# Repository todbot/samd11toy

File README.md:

# samd11toy
playing with SAMD11

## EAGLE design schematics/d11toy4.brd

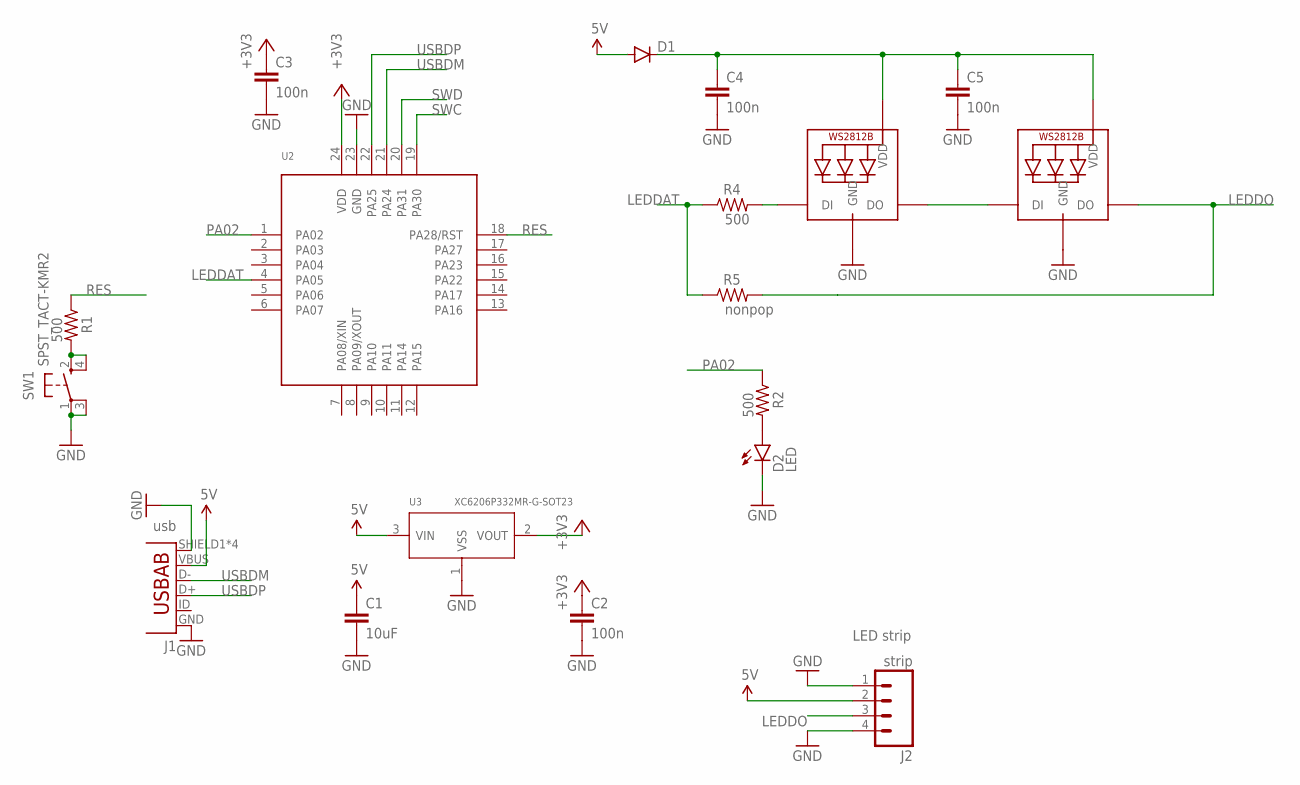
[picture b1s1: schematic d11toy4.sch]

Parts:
C1: 10uF; 0603-CAP
C2, C3, C4, C5: 100n; 0603-CAP
D1: DIODESOD523; SOD523
D2: LED; LED-0603
J1: usb; USB-AB-MICRO-SMD
J2: strip; 1X04_NO_SILK_ALL_ROUND
LED1, LED2: WS2812B5050; WS2812B
R1, R2, R4: 500; 0603-RES
R5: nonpop; 0603-RES
SW1: SPST_TACT-KMR2; KMR2
U2: SAMD11D14AM; QFN24
U3: XC6206P332MR-G-SOT23; SOT-23

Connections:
5V: C1.1, D1.A, J1.VBUS, J2.2, U3.3 (VIN)
+3V3: C2.1, C3.1, U2.24 (VDD), U3.2 (VOUT)
GND: C1.2, C2.2, C3.2, C4.2, C5.2, D2.C, J1.GND, J1.SHIELD1 (SHIELD), J1.SHIELD2 (SHIELD), J1.SHIELD3 (SHIELD), J1.SHIELD4 (SHIELD), J2.1, J2.4, LED1.3-GND (GND), LED2.3-GND (GND), SW1.1, SW1.3 (P1), U2.23 (GND), U3.1 (VSS)
LEDDAT: R4.1, R5.1, U2.4 (PA05)
LEDDO: J2.3, LED2.2-DOUT (DO), R5.2
unnamed: D2.A, R2.2
unnamed: R1.2, SW1.2 (S), SW1.4 (S1)
unnamed: LED1.2-DOUT (DO), LED2.4-DIN (DI)
unnamed: C4.1, C5.1, D1.C, LED1.1-VDD (VDD), LED2.1-VDD (VDD)
unnamed: LED1.4-DIN (DI), R4.2
PA02: R2.1, U2.1 (PA02)
RES: R1.1, U2.18 (PA28/RST)
SWC: U2.19 (PA30)
SWD: U2.20 (PA31)
USBDM: J1.D-, U2.21 (PA24)
USBDP: J1.D+, U2.22 (PA25)

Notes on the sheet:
LED strip

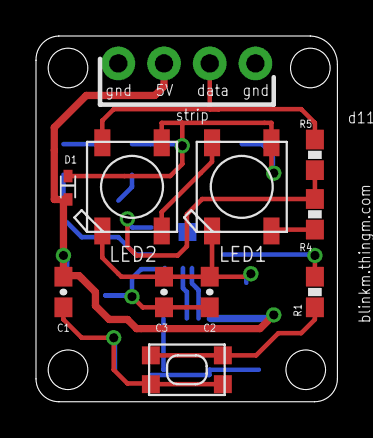
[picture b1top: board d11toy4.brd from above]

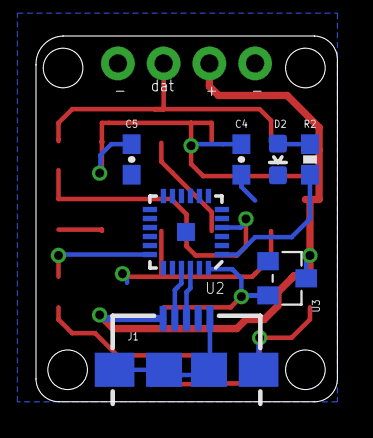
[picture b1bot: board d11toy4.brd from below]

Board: 2 copper layers, 16.7 x 20.3 mm, 18 parts (7 on the bottom side), 14 nets.

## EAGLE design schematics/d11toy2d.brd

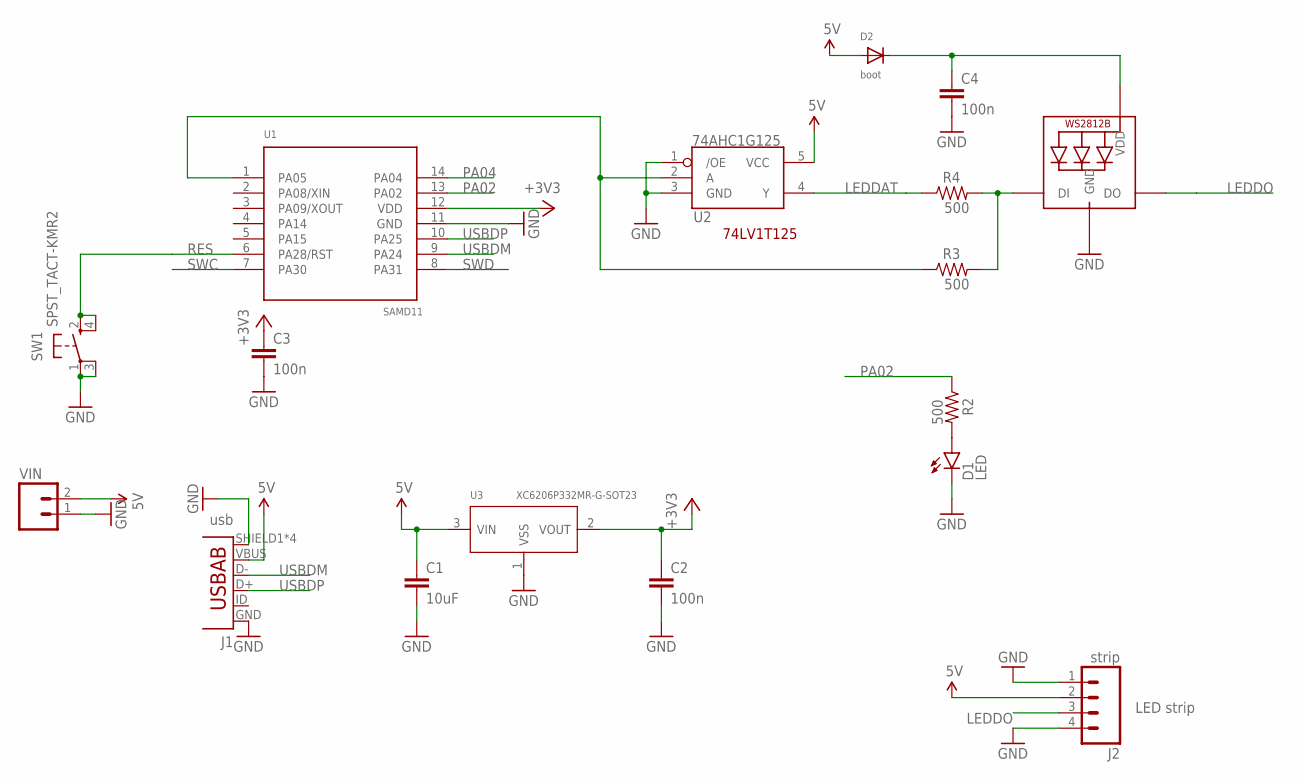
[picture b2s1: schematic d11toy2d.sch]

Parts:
C1: 10uF; 0603-CAP
C2, C3, C4: 100n; 0603-CAP
D1: LED; LED-0603
D2: boot; SOD-523
J1: usb; USB-AB-MICRO-SMD
J2: strip; 1X04_NO_SILK_ALL_ROUND
LED1: WS2812B5050; WS2812B
R2, R3, R4: 500; 0603-RES
SW1: SPST_TACT-KMR2; KMR2
U1: SAMD11; SO14
U2: 74AHC1G125; SOT23-5
U3: XC6206P332MR-G-SOT23; SOT-23
VIN: M02PTH; 1X02

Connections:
5V: C1.1, D2.A, J1.VBUS, J2.2, U2.5 (VCC), U3.3 (VIN), VIN.2
+3V3: C2.1, C3.1, U1.12 (VDD), U3.2 (VOUT)
GND: C1.2, C2.2, C3.2, C4.2, D1.C, J1.GND, J1.SHIELD1 (SHIELD), J1.SHIELD2 (SHIELD), J1.SHIELD3 (SHIELD), J1.SHIELD4 (SHIELD), J2.1, J2.4, LED1.3-GND (GND), SW1.1, SW1.3 (P1), U1.11 (GND), U2.1 (/OE), U2.3 (GND), U3.1 (VSS), VIN.1
LEDDAT: R4.1, U2.4 (Y)
LEDDAT3V3: R3.1, U1.1 (PA05), U2.2 (A)
LEDDO: J2.3, LED1.2-DOUT (DO)
unnamed: D1.A, R2.2
unnamed: C4.1, D2.K (C), LED1.1-VDD (VDD)
unnamed: LED1.4-DIN (DI), R3.2, R4.2
PA02: R2.1, U1.13 (PA02)
PA04: U1.14 (PA04)
RES: SW1.2 (S), SW1.4 (S1), U1.6 (PA28/RST)
SWC: U1.7 (PA30)
SWD: U1.8 (PA31)
USBDM: J1.D-, U1.9 (PA24)
USBDP: J1.D+, U1.10 (PA25)

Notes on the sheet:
LED strip
74LV1T125

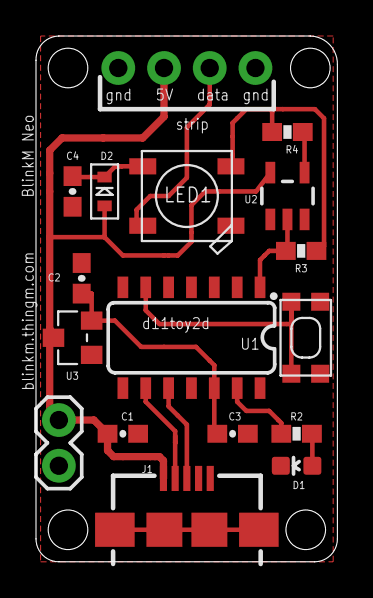
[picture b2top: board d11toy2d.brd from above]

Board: 2 copper layers, 16.7 x 29.2 mm, 17 parts (0 on the bottom side), 13 nets.

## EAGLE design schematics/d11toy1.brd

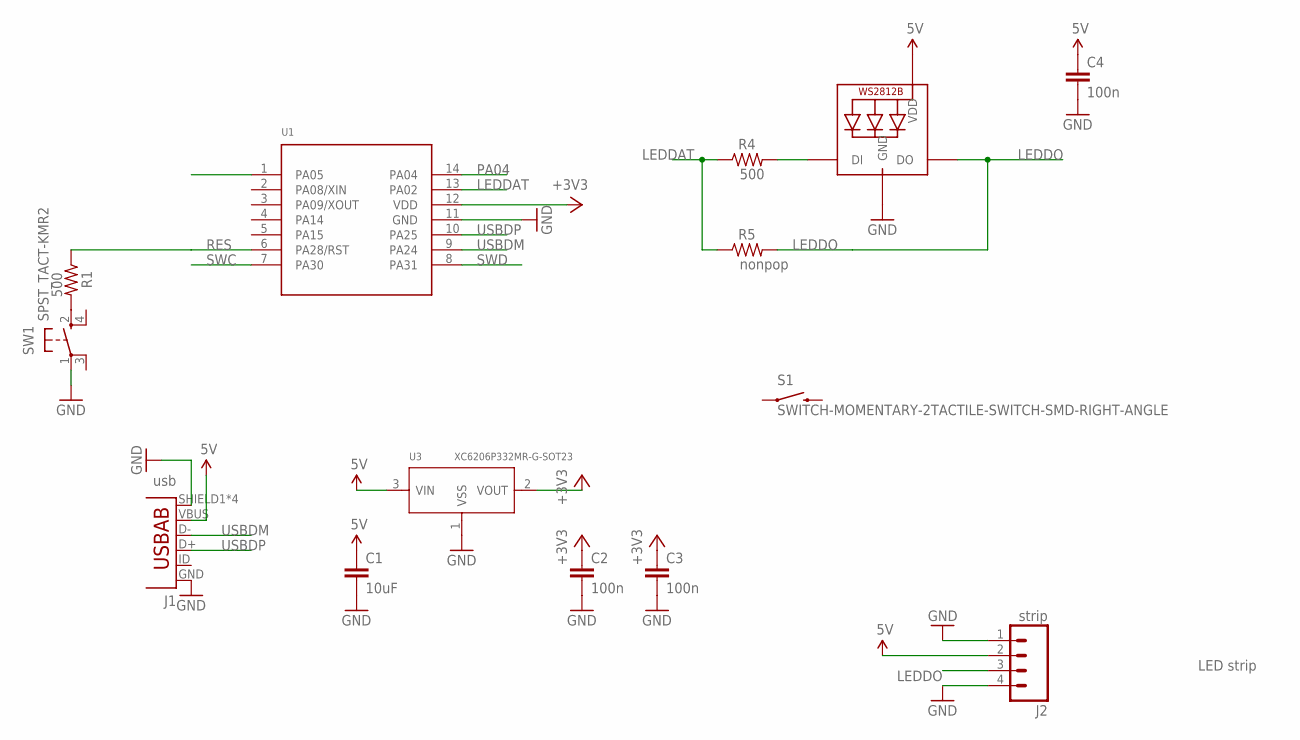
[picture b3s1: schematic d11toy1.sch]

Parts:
C1: 10uF; 0603-CAP
C2, C3, C4: 100n; 0603-CAP
J1: usb; USB-AB-MICRO-SMD
J2: strip; 1X04_NO_SILK_ALL_ROUND
LED1: WS2812B3535; LED3535
R1, R4: 500; 0603-RES
R5: nonpop; 0603-RES
S1: SWITCH-MOMENTARY-2TACTILE-SWITCH-SMD-RIGHT-ANGLE; TACTILE_SWITCH-SMD-RIGHT-ANGLE
SW1: SPST_TACT-KMR2; KMR2
U1: SAMD11C14; SO14
U3: XC6206P332MR-G-SOT23; SOT-23

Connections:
5V: C1.1, C4.1, J1.VBUS, J2.2, LED1.2 (VDD), U3.3 (VIN)
+3V3: C2.1, C3.1, U1.12 (VDD), U3.2 (VOUT)
GND: C1.2, C2.2, C3.2, C4.2, J1.GND, J1.SHIELD1 (SHIELD), J1.SHIELD2 (SHIELD), J1.SHIELD3 (SHIELD), J1.SHIELD4 (SHIELD), J2.1, J2.4, LED1.4 (GND), SW1.1, U1.11 (GND), U3.1 (VSS)
LEDDAT: R4.1, R5.1, U1.13 (PA02)
LEDDO: J2.3, LED1.3 (DO), R5.2
unnamed: R1.2, SW1.2 (S)
unnamed: LED1.1 (DI), R4.2
PA04: U1.14 (PA04)
RES: R1.1, U1.6 (PA28/RST)
SWC: U1.7 (PA30)
SWD: U1.8 (PA31)
USBDM: J1.D-, U1.9 (PA24)
USBDP: J1.D+, U1.10 (PA25)

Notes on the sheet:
LED strip

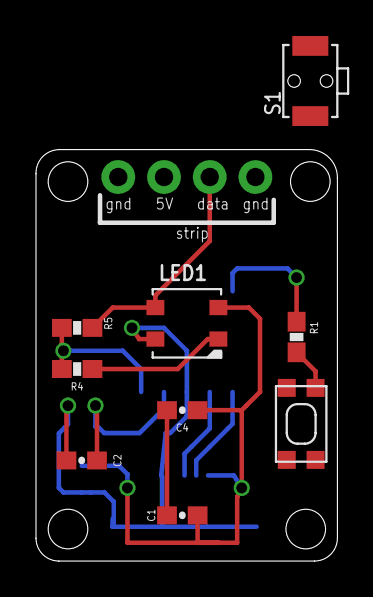
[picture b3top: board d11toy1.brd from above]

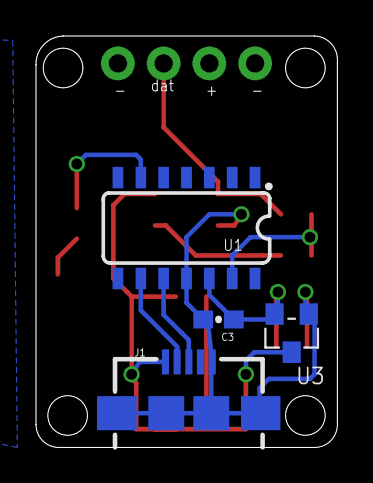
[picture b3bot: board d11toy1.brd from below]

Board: 2 copper layers, 16.7 x 22.9 mm, 14 parts (4 on the bottom side), 10 nets.

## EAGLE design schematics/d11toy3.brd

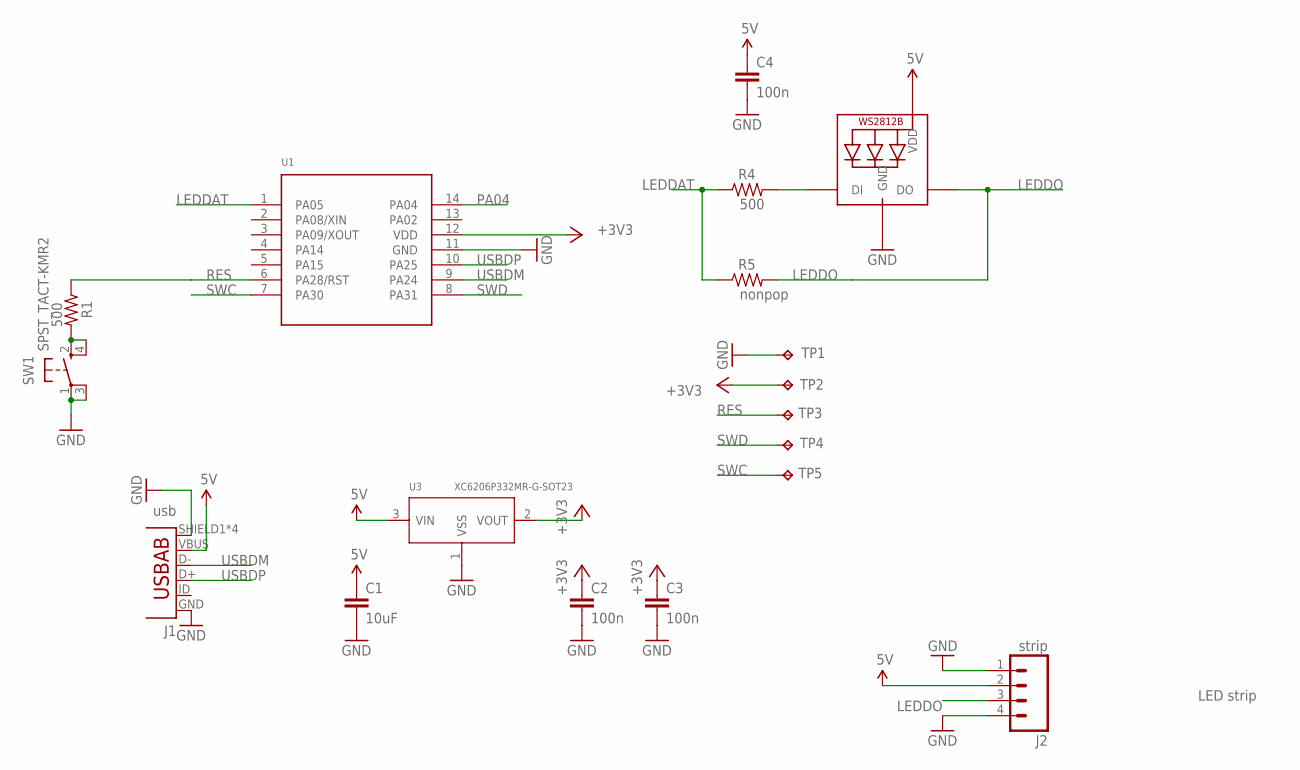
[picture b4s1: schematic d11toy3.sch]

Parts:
C1: 10uF; 0603-CAP
C2, C3, C4: 100n; 0603-CAP
J1: usb; USB-AB-MICRO-SMD
J2: strip; 1X04_NO_SILK_ALL_ROUND
LED2: WS2812B5050; WS2812B
R1, R4: 500; 0603-RES
R5: nonpop; 0603-RES
SW1: SPST_TACT-KMR2; KMR2
TP1, TP2, TP3, TP4, TP5: TPB1,27; B1,27
U1: SAMD11C14; SO14
U3: XC6206P332MR-G-SOT23; SOT-23

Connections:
5V: C1.1, C4.1, J1.VBUS, J2.2, LED2.1-VDD (VDD), U3.3 (VIN)
+3V3: C2.1, C3.1, TP2.TP, U1.12 (VDD), U3.2 (VOUT)
GND: C1.2, C2.2, C3.2, C4.2, J1.GND, J1.SHIELD1 (SHIELD), J1.SHIELD2 (SHIELD), J1.SHIELD3 (SHIELD), J1.SHIELD4 (SHIELD), J2.1, J2.4, LED2.3-GND (GND), SW1.1, SW1.3 (P1), TP1.TP, U1.11 (GND), U3.1 (VSS)
LEDDAT: R4.1, R5.1, U1.1 (PA05)
LEDDO: J2.3, LED2.2-DOUT (DO), R5.2
unnamed: R1.2, SW1.2 (S), SW1.4 (S1)
unnamed: LED2.4-DIN (DI), R4.2
PA04: U1.14 (PA04)
RES: R1.1, TP3.TP, U1.6 (PA28/RST)
SWC: TP5.TP, U1.7 (PA30)
SWD: TP4.TP, U1.8 (PA31)
USBDM: J1.D-, U1.9 (PA24)
USBDP: J1.D+, U1.10 (PA25)

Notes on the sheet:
LED strip

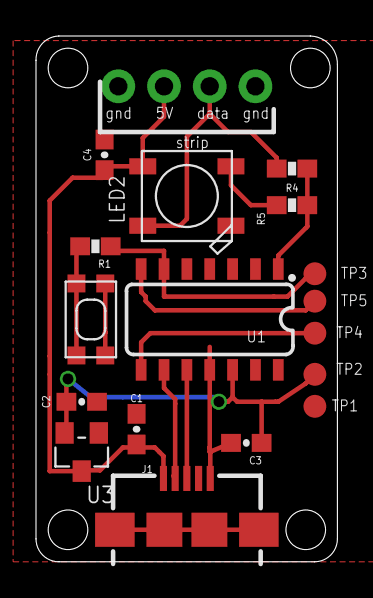
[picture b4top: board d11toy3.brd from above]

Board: 2 copper layers, 16.7 x 29.2 mm, 18 parts (0 on the bottom side), 12 nets.

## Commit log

2016-10-24 more experiments

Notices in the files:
parts and their libraries:
SparkFun-Connectors: Licensing: Creative Commons ShareAlike 4.0 International - https://creativecommons.org/licenses/by-sa/4.0
